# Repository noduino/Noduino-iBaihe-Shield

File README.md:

Noduino iBaihe Board
=======================================

[*Noduino iBaihe Board - Complete iBaihe board (iBaihe V1.0)*](https://www.noduino.org/)

[*Noduino iBaihe Board Bottom - Complete iBaihe board*](https://www.noduino.org/)

Overview
-------------------
There are 5 Relays in the iBaihe board. It's designed for home automation.

iBaihe V2.0 is a 5 relays Standalone version that use a NodeC module (a coin-sized ESP8285 module).

iBaihe V1.0 is a arduino-compatible 5 relays shield.

[*Noduino NodeC WiFi Module*](https://www.noduino.org/products/nodec)

The pin map of iBaihe v2.0 Board:

* D3	(GPIO15)  ---> control the 5th relay

* D4	(GPIO13)  ---> control the 1st relay
* D5	(GPIO12)  ---> control the 2nd relay
* D6	(GPIO14)  ---> control the 3rd relay
* D7	(GPIO16)  ---> control the 4th relay

* D8	(GPIO4)   ---> as i2c SDA
* D9	(GPIO5)   ---> as i2c SCL

* D10	(GPIO0)   ---> input key
* D0	(GPIO3)   ---> WiFI Status LED

The pin map of iBaihe v1.0 shield board:

* D4	(GPIO13)  ---> control the 1st relay
* D5	(GPIO12)  ---> control the 2nd relay
* D6	(GPIO14)  ---> control the 3rd relay
* D7	(GPIO16)  ---> control the 4th relay

* D8	(GPIO4)   ---> control the 5th relay

* D10	(GPIO0)   ---> input key

Repository Contents
-------------------
* V2.0/ - All Eagle desgin files (.brd, .sch) and Gerber files of iBaihe v2.0
* V1.0/ - All Eagle design files (.brd, .sch) and Gerber files of iBaihe v1.0 shield

Product Versions
----------------
* [FALCON-100](http://www.noduino.org/) - As a 5 relays shield for Falcon/Quantum board.
* [FALCON-200](http://www.noduino.org/) - 5 relays Standalone version using a NodeC module (Our coin-sized ESP8285 module).

License Information
-------------------
The hardware is released under [Creative Commons ShareAlike 4.0 International](https://creativecommons.org/licenses/by-sa/4.0/).

Distributed as-is; no warranty is given.

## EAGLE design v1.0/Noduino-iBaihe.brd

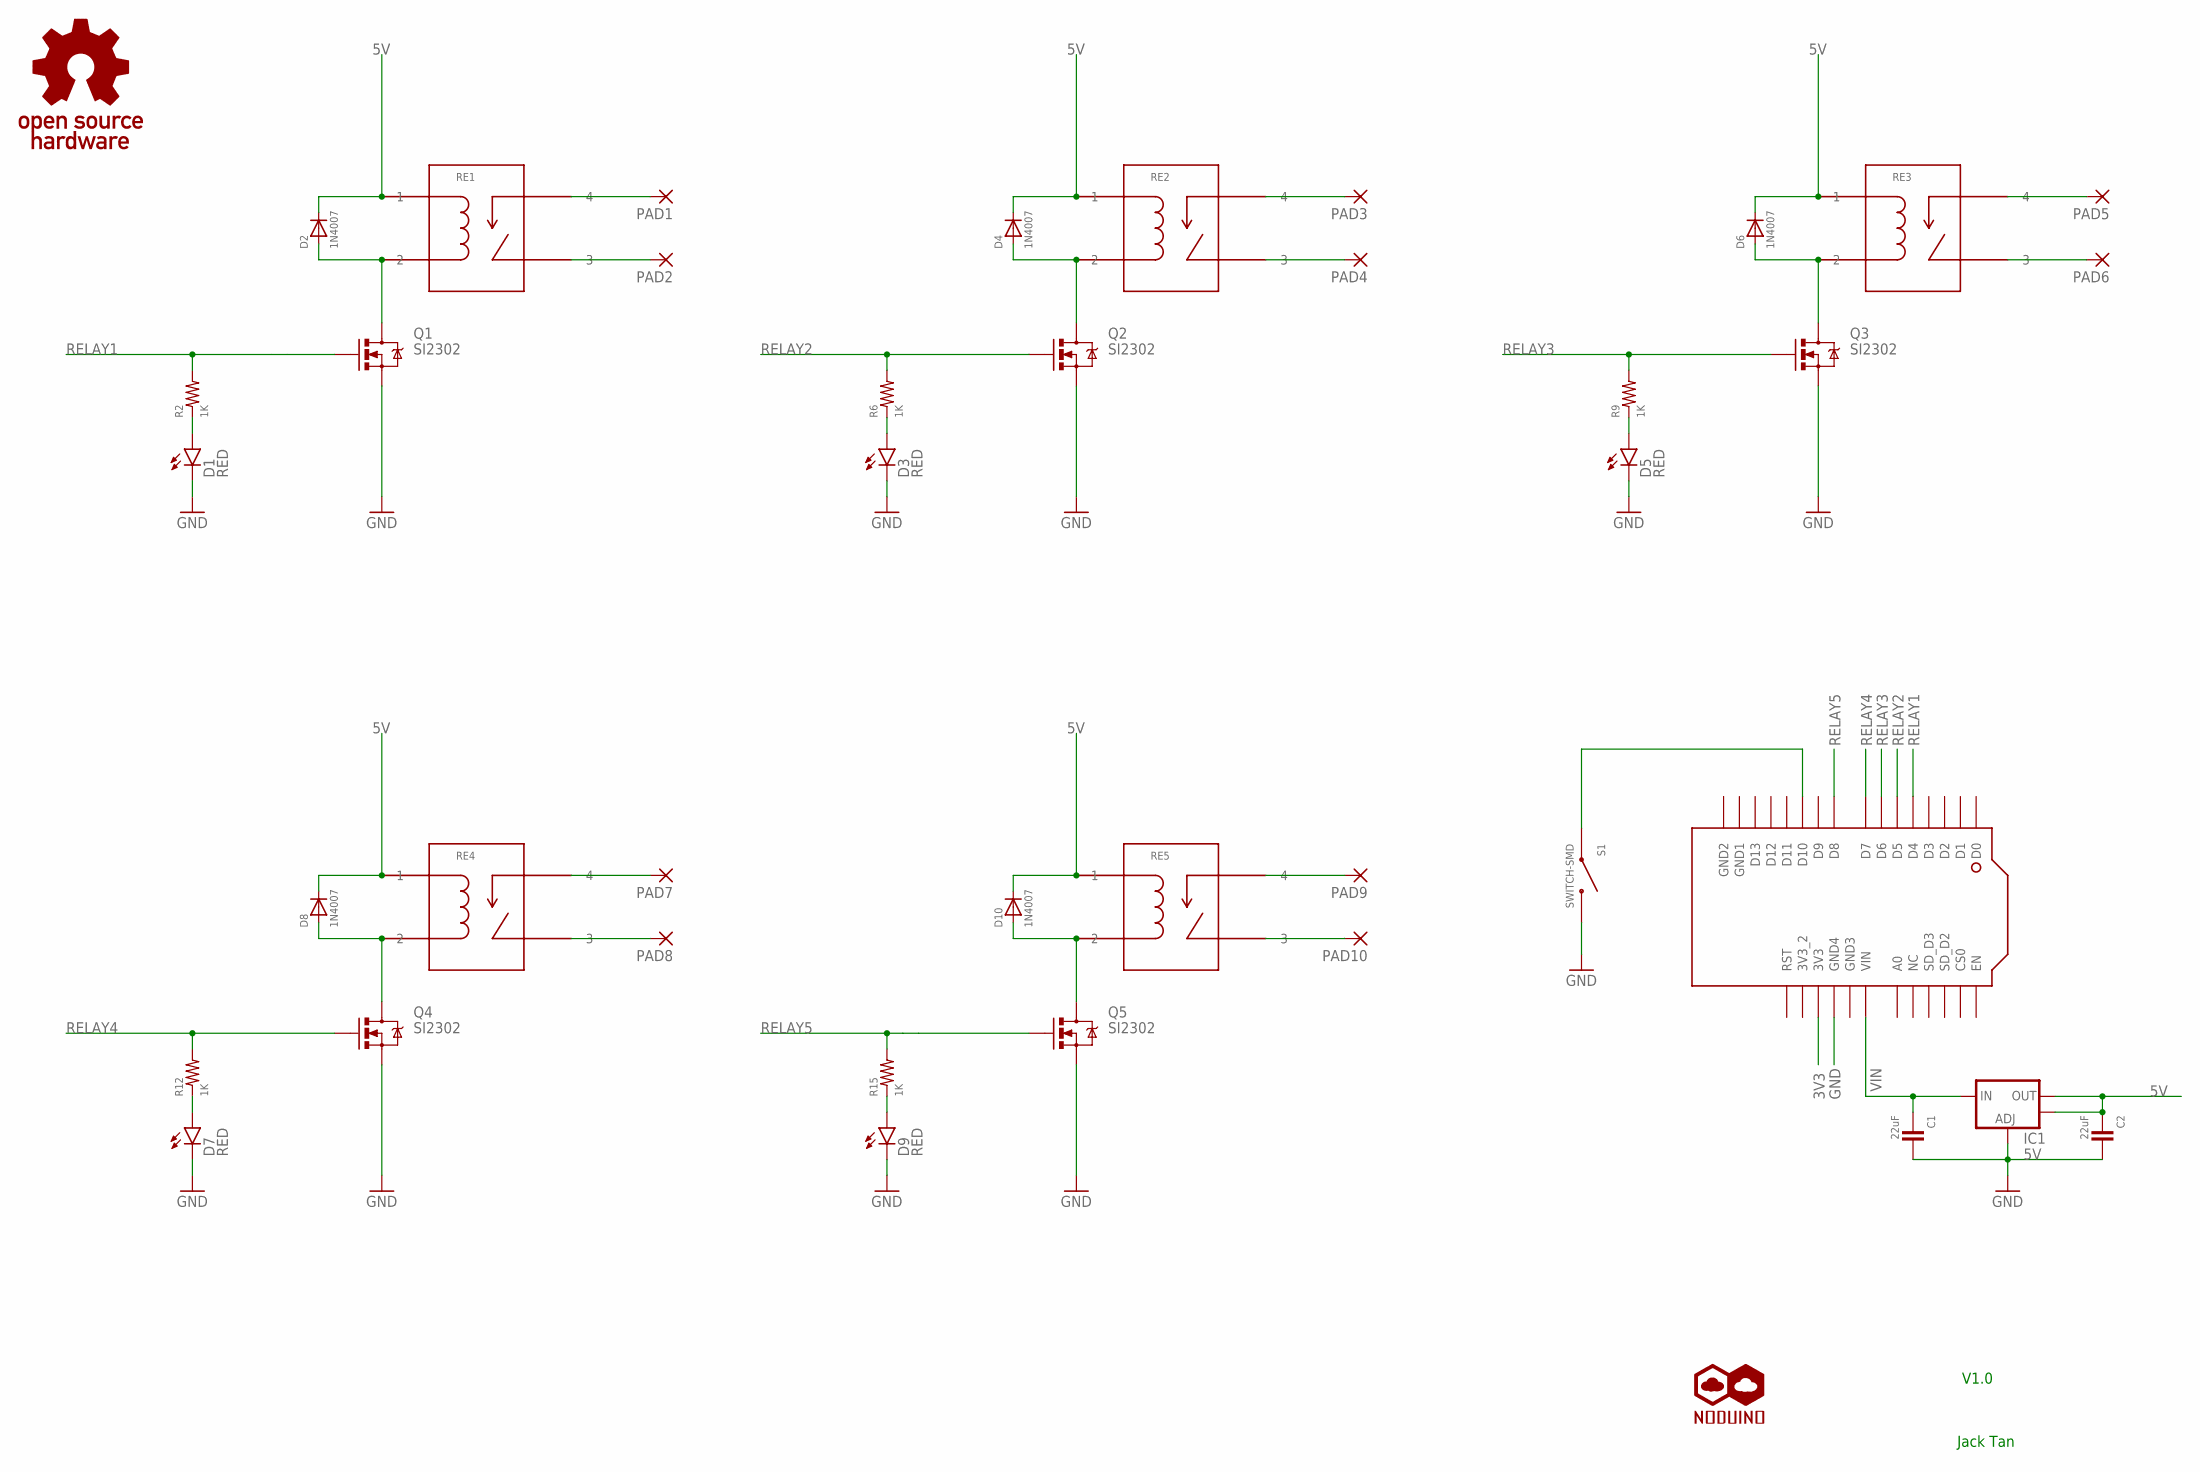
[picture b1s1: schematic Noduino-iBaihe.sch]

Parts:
C1, C2: 22uF; C1206
D1, D3, D5, D7, D9: RED; LED-0603
D2, D4, D6, D8, D10: 1N4007; SOD-323
IC1: 5V; SOT223
N1: NODUINO-PINMAIL; NODUINO-PIN-MAIL
PAD1, PAD2, PAD3, PAD4, PAD5, PAD6, PAD7, PAD8, PAD9, PAD10: 2,15/1,0
Q1, Q2, Q3, Q4, Q5: SI2302; SOT23-3
R2, R6, R9, R12, R15: 1K; 0603-RES
RE1, RE2, RE3, RE4, RE5: HKE-HRS3FNH; HKE-HRS3FN
S1: SWITCH-SMD; TACTILE-SWITCH-1101NE
U$1: NODUINO-LOGO-ALL; NODUINO-ALL-1
U$2: OPEN_HARDWARE_LOGO

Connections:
3V3: N1.P$26 (3V3)
5V: C2.1, D2.1 (C), D4.1 (C), D6.1 (C), D8.1 (C), D10.1 (C), IC1.2 (OUT), IC1.4 (OUT), RE1.1, RE2.1, RE3.1, RE4.1, RE5.1
GND: C1.2, C2.2, D1.C, D3.C, D5.C, D7.C, D9.C, IC1.1 (ADJ), N1.P$25 (GND4), Q1.2 (S), Q2.2 (S), Q3.2 (S), Q4.2 (S), Q5.2 (S), S1.P$1 (1)
unnamed: D2.2 (A), Q1.3 (D), RE1.2
unnamed: PAD1.1, RE1.4
unnamed: D1.A, R2.1
unnamed: PAD2.1, RE1.3
unnamed: D3.A, R6.1
unnamed: D4.2 (A), Q2.3 (D), RE2.2
unnamed: PAD3.1, RE2.4
unnamed: PAD4.1, RE2.3
unnamed: D5.A, R9.1
unnamed: D6.2 (A), Q3.3 (D), RE3.2
unnamed: PAD5.1, RE3.4
unnamed: PAD6.1, RE3.3
unnamed: D7.A, R12.1
unnamed: D8.2 (A), Q4.3 (D), RE4.2
unnamed: PAD7.1, RE4.4
unnamed: PAD8.1, RE4.3
unnamed: D9.A, R15.1
unnamed: D10.2 (A), Q5.3 (D), RE5.2
unnamed: PAD9.1, RE5.4
unnamed: PAD10.1, RE5.3
unnamed: N1.P$11 (D10), S1.P$2 (2)
RELAY1: N1.P$5 (D4), Q1.1 (G), R2.2
RELAY2: N1.P$6 (D5), Q2.1 (G), R6.2
RELAY3: N1.P$7 (D6), Q3.1 (G), R9.2
RELAY4: N1.P$8 (D7), Q4.1 (G), R12.2
RELAY5: N1.P$9 (D8), Q5.1 (G), R15.2
VIN: C1.1, IC1.3 (IN), N1.P$23 (VIN)

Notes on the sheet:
Jack Tan
V1.0

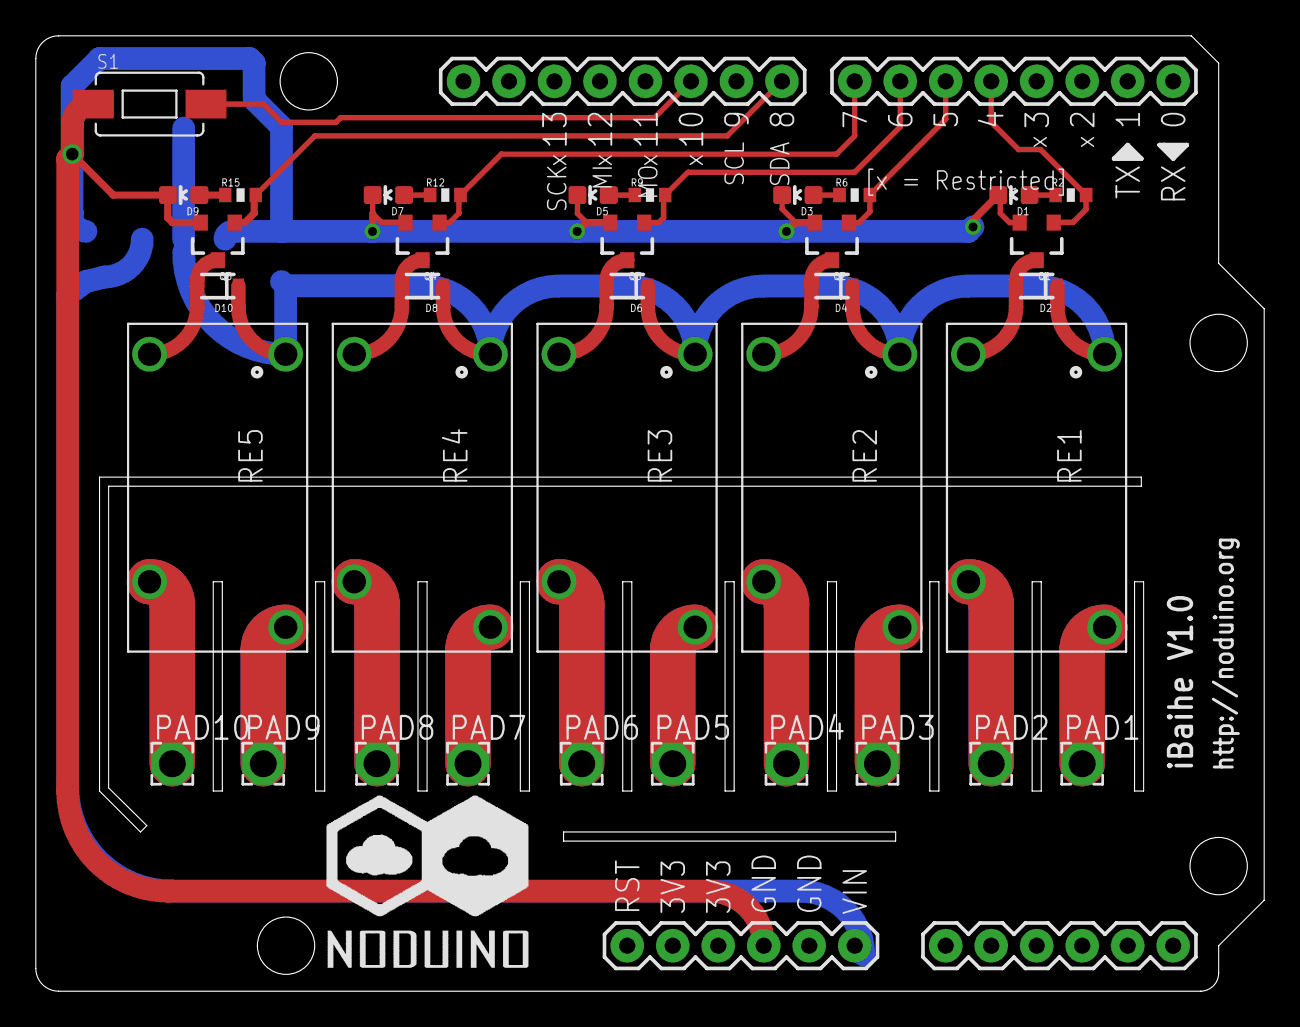
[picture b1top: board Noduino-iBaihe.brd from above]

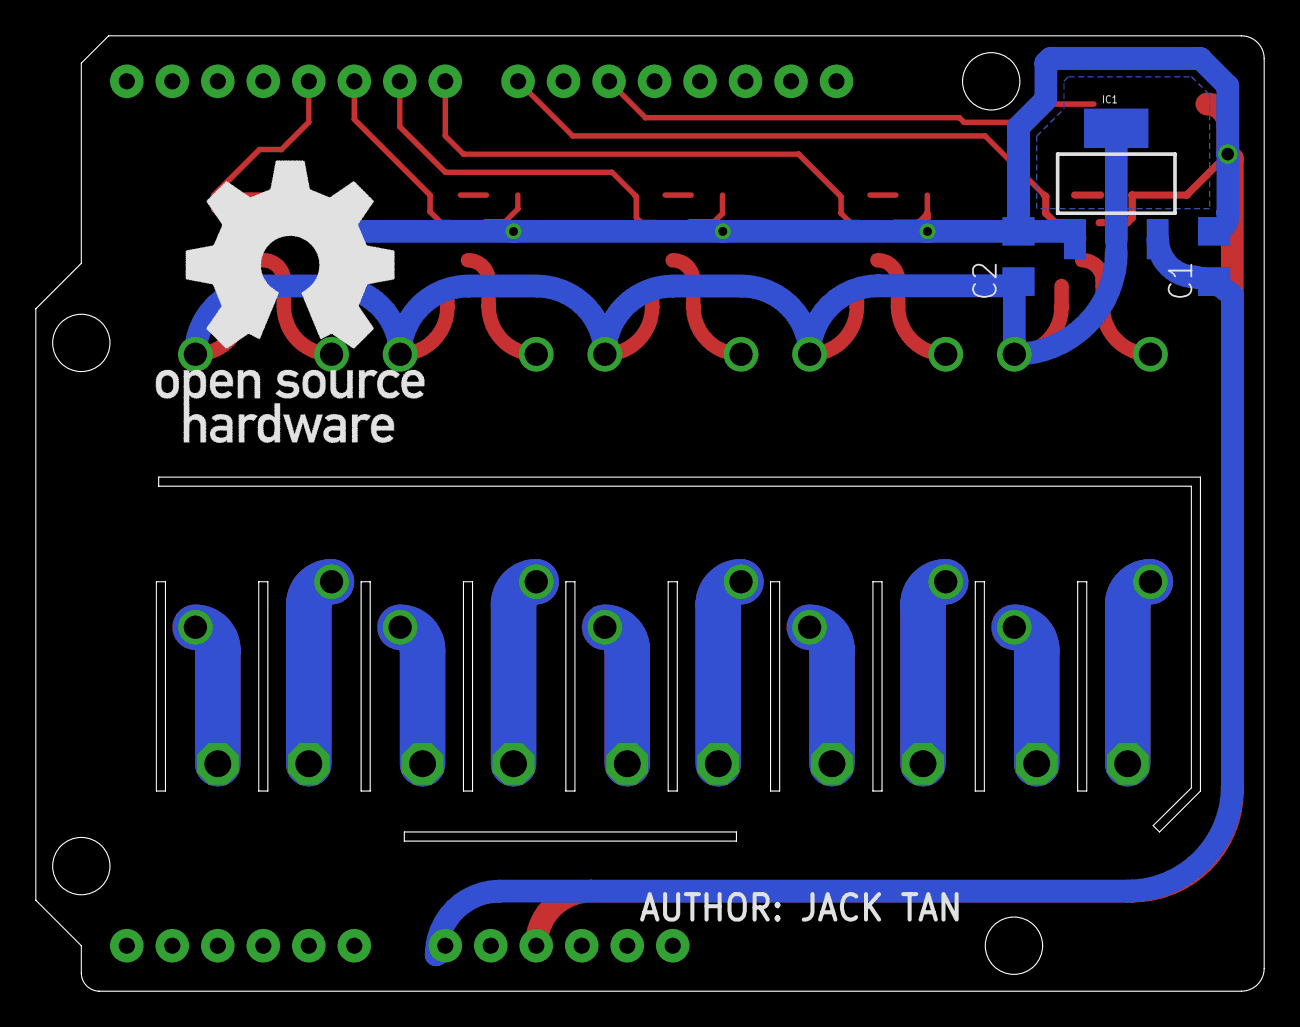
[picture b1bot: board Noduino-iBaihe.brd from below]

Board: 2 copper layers, 68.6 x 53.3 mm, 42 parts (4 on the bottom side), 29 nets.

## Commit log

2016-09-30 add the ibaihe v2.0 sch and layout files
    eagle format
2016-09-30 add the ibaihe version 1.0 eagle designed files
2016-09-30 add the readme and board images
2016-09-30 fixup the readme
2016-09-30 add the board image of ibaihe v1.0
2016-09-30 update the readme
2016-09-30 add the nodec image and update the readme
2016-10-01 change the drill size of pins interface to 0.9mm
    The old drill size of v1.0 shield is 0.7mm.
    It's too small
